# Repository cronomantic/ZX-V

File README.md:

**English** · [Español](README.es.md)

<h1 align="center">
  <picture>
    <source media="(prefers-color-scheme: dark)" srcset="docs/images/logo-dark.svg">
    
  </picture>
</h1>

A 32-bit hobby computer inspired by the ZX Spectrum. It is not a Spectrum
clone or a Spectrum emulator: it is a new machine that keeps the spirit of the
original — switch it on and you are in BASIC, ready to type a program.

- **The Spectrum's 15 colours, without colour clash:** every pixel has its own
  colour.
- **A BASIC compatible with Sinclair BASIC** (as far as is reasonable), with a
  full-screen editor and many extensions: structured loops, procedures,
  sprites, tile maps, scrolling, music and files.
- **Sound** from two AY-3-8912 chips and the beeper.
- **An SD card** instead of the tape: it also loads the Spectrum's `.TAP` and
  `.TZX` files. Examples and games come built in, on the `ROM:` drive.
- **Native programs in C** for its RISC-V CPU — the equivalent of Z80 machine
  code games — with an SDK, and BASIC compiled with
  [ZX Basic](docs/en/zxbasic.md).
- **An emulator** for Windows, Linux and the web browser.
- **Real hardware** built with two Raspberry Pi Pico 2 boards: one is the CPU,
  the other the "ULA" (video and sound).

> **Status:** the emulator and the ROM with BASIC work, and so does the first
> printed circuit board, with the two Picos together: the picture, the sound,
> the USB ports, the microSD card, the clock with its coin cell and loading
> from the PC through J5.

## Try it

**In your browser:** [zx-v.org/emulator](https://zx-v.org/emulator/),
nothing to install. The project's website, with its games to play right
there, is [zx-v.org](https://zx-v.org/).

**On your computer:** download the latest version from
[**Releases**](https://github.com/cronomantic/ZX-V/releases):

| Package | What it is |
|---|---|
| `zxv-windows-x64.zip` | The emulator for Windows, with the ROM and the examples |
| `zxv-linux-x86_64.tar.gz` and the `.AppImage` | The emulator for Linux |
| `zxv-web.zip` | The web version: unzip it and open `index.html` (no server needed) |
| `zxv-uf2.zip` | The firmware for the two Picos of the real machine |

Open it and you are in BASIC. Type this, pressing Enter after each line:

```
10 FOR i=1 TO 8: CIRCLE INK i;128,88,i*10: NEXT i
RUN
```

Then try `CAT "ROM:"` to see the built-in examples and games... or start with
the [getting started guide](docs/en/getting-started.md).

## Documentation

| | |
|---|---|
| [Getting started](docs/en/getting-started.md) | From zero to your first program |
| [Learn BASIC](docs/en/basic/README.md) | A course from scratch, step by step |
| [BASIC reference](docs/en/basic/reference.md) · [The editor](docs/en/basic/editor.md) | Every statement and function |
| [Native programs (SDK)](docs/en/sdk/README.md) | Programming the machine in C |
| [Graphics](docs/en/sdk/graphics.md#the-graphics-editor-for-the-pc-zxv-gfx) · [Music](docs/en/sdk/README.md#the-tracker-for-the-pc-zxv-tracker) | The editors for the PC: `zxv-gfx` and `zxv-tracker` |
| [Compiling BASIC](docs/en/zxbasic.md) | ZX Basic, with a target for ZX-V |
| [The emulator](docs/en/emulator.md) | The desktop and web versions, options |
| [The machine](docs/en/machine.md) | Screen, colours, sound, memory and files |
| [Build the hardware](docs/en/hardware/README.md) | The board, assembly and firmware |

All of it is also in Spanish: [docs/es](docs/es/README.md). And on the
web, with an index to move around: [zx-v.org/docs](https://zx-v.org/docs/en/).

## How it is made

```
┌────────── Pico 2 "CPU" ──────────┐   8-bit link + clock   ┌────────── Pico 2 "ULA" ──────────┐
│ the ROM: BASIC and the system    │───────────────────────►│ video: HDMI / DVI                │
│ your programs                    │   sound line           │ sound: two AY chips + beeper     │
│ USB keyboard, mouse and gamepads │───────────────────────►│        over HDMI and line out    │
│ SD card, clock                   │◄───────────────────────│                                  │
└──────────────────────────────────┘   frame sync, return   └──────────────────────────────────┘
```

For software there is a single machine; that it is made of two chips is a
detail of the hardware, and the emulator implements the same machine in one
program.

## What is here

| | |
|---|---|
| [`sdk/`](sdk) | The SDK for native programs in C, with its examples and eight complete games in C. MIT licence ([`sdk/LICENSE`](sdk/LICENSE)): your programs can have any licence |
| [`examples/`](examples) | Games in BASIC (`basic/`) and two in compiled BASIC with ZX Basic (`zxbasic/stardust` and `zxbasic/petitsoccer`). MIT licence ([`examples/LICENSE`](examples/LICENSE)) |
| [`docs/`](docs) | The documentation, in English and Spanish. CC BY 4.0 licence ([`docs/LICENSE`](docs/LICENSE)), the same as `dev/`; its code examples are public domain |
| [`pcb/`](pcb) | The printed circuit board, revision 1: the KiCad project, the files to order it from JLCPCB and the scripts that made it. Open hardware, CERN-OHL-W v2 licence ([`pcb/LICENSE`](pcb/LICENSE), with the exceptions in [`pcb/NOTICE`](pcb/NOTICE)); the scripts, MIT |
| [`dev/`](dev) | The technical specification of the machine ([`spec.md`](dev/spec.md)) and of its BASIC ([`basic.md`](dev/basic.md)), in Spanish: memory map, registers, the ROM API, file formats |
| [Releases](https://github.com/cronomantic/ZX-V/releases) | The emulator, the ROM and the firmware, as binaries. Free, and you can pass them on unchanged and free of charge: the terms are in [`TERMS.txt`](TERMS.txt) |

The source code of the emulator, the ROM and the firmware is not public. The
packages say in their `THIRD_PARTY_NOTICES.txt` what they contain that belongs
to others, with the texts of those licences.

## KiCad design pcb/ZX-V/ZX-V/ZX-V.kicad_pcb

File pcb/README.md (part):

# La placa de ZX-V

> **Using ZX-V?** See the board guide: [English](../docs/en/hardware/board.md) · [Español](../docs/es/hardware/board.md). This page is developer documentation, in Spanish.  
> **¿Usas ZX-V?** Mira la guía de la placa: [English](../docs/en/hardware/board.md) · [Español](../docs/es/hardware/board.md). Esta página es documentación de desarrollo.

**Estado: revisión 1 (v0.1), fabricada y probada:** con las dos Pico pasa `boardtest`, usa la tarjeta microSD y, con la pila, el reloj guarda la hora. Licencia CERN-OHL-W v2 (§8). El esquema (85 piezas en
tres hojas: alimentación, Pico CPU y Pico ULA) lo dibuja `tools/schematic.py`,
con ERC sin errores y cada pieza con su número LCSC. Las huellas que no traía
KiCad están en `zxv.pretty`, comprobadas con los planos. La placa la ponen al
día `tools/netlist_to_board.py` (del netlist), `tools/place.py` (contorno,
taladros, reglas y el sitio de cada pieza) y `tools/silkscreen.py` (los
rótulos propios y las referencias, cada una en un hueco libre). El rutado, en
dos pasos (§4.6): `tools/pairs.py` traza a mano los pares diferenciales (los
cuatro del HDMI y el del USB), y `tools/route.py` pasa el resto a Freerouting y
pone la masa: un plano en cada cara y vías de cosido. DRC: paridad con el
esquema, 0; nada sin conectar, sin errores de margen ni de serigrafía. Solo
queda el aviso de que las Pico no coinciden con su huella de la biblioteca: es
la marca *DNP* que les pone el esquema. Las dos Pico 2 y todo lo de la
protoboard en una placa. Los pines, los valores y por qué son los que son
están en dev/hardware-pico.md; aquí, lo propio de
la placa. El proyecto de KiCad (10) está en `ZX-V/ZX-V/`.

---

## 1. Objetivos

- **Que la pueda montar cualquiera**, de tres maneras (decisiones D57):
  1. **Pedirla montada a JLCPCB:** todo es SMD de una cara, así que vale su
     montaje *Economic*, el barato. Llega con todo soldado salvo las dos
     Pico, que se sueldan con sus tiras de pines (THT, lo más fácil de
     soldar; §6.2).
  2. **Con soldador:** todo lo SMD se puede soldar a mano.
  3. **Con placa caliente u horno:** con el stencil, que se pide con las
     placas.
- **De 100 × 100 mm o menos**, el tamaño más barato de JLCPCB, y **de dos
  capas**, con plano de masa.
- **Todo lo de la protoboard**, y nada que el firmware no use, salvo lo que
  cuesta un par de pads (§3).

---

## 2. Reglas del diseño

- **Todo lo SMD en la cara de arriba:** una placa caliente no suelda las dos
  caras, y JLCPCB monta una sola más barato.
- **Nada pequeño:** pasivos de 0805 con las huellas `_HandSolder` (los pads
  más largos); chips en SOIC, SOT-23 o SOD-123, sin QFN ni pads escondidos
  debajo. Sitio alrededor de cada pieza para la punta del soldador. La
  excepción, el cristal del reloj (3,2 × 1,5 mm, dos pads): es la pieza
  *Basic*, y se suelda bien con flux.
- **Cada pieza SMD con su número LCSC**, en el campo `LCSC` del símbolo. Las
  *Basic* de JLCPCB siempre que se pueda: las *Extended* cuestan más al
  montar.
- **Nada THT en el montaje:** JLCPCB cobra aparte cada soldadura THT, y con
  una sola el pedido ya no vale para el *Economic*. Solo son THT las tiras
  de las Pico (no los hay SMD de 1 × 20), las tiras opcionales y los mandos
  y LED del frontal (en ángulo recto, para que salgan por la caja), y los
  suelda quien la monta: van marcados *DNP*.
- **La serigrafía**, para montarla sin el esquema: referencias y valores, la
  polaridad de diodos, LED, condensadores y pila, los nombres de los
  conectores y los de los pines de las tiras.
- **En el repositorio**, con cada versión: el esquema en PDF, el BOM y el CPL
  de JLCPCB, los Gerber y la guía de montaje (la de la placa, en
  [inglés](../docs/en/hardware/board.md) y en [español](../docs/es/hardware/board.md)).

---

## 3. Decisiones de la placa (propuestas)

| Qué | Propuesta | Por qué |
|---|---|---|
| Las Pico | **Con tiras macho de 1 × 20**, soldadas a la Pico y a los taladros de la placa, o **por sus bordes almenados**: la huella común de KiCad (`RaspberryPi_Pico_Common_Unspecified`) tiene a la vez los taladros y los pads, y una zona libre para el enchufe del micro-USB. Va copiada en `zxv:RaspberryPi_Pico2_Common`, sin la zona prohibida de la antena de la Pico W, que la Pico 2 no tiene | Con las tiras, lo de siempre: separada de la placa, quedan a mano el micro-USB, el BOOTSEL y el conector de depuración (SWD) para el cable de programar. Almenada, la mitad de soldaduras y más baja |
| Módulos | **Ninguno:** la microSD, el reloj y el HDMI, en la placa | Más barato, más bajo y sin cables |
| Alimentación | **USB-C solo para la corriente**, de 5 V | Vale cualquier cargador de 2 A; no hay que comprar una fuente aparte |
| Capas | **Dos**, con plano de masa en las dos caras | El HDMI sale de GPIO con una resistencia en serie y pistas de 2 a 3 cm: los pares van acoplados, igualados y con el plano entero debajo (§4.6), pero sin impedancia controlada (con el plano a 1,5 mm no se llega a 100 Ω), que a 252 Mbit/s no decide. El USB es de 12 Mbit/s |
| Reinicio | **Un pulsador** a los RUN de las dos Pico | Sin desenchufar; Ctrl+Alt+Supr reinicia toda la Pico CPU, pero no la ULA |
| Encendido | **Un deslizante** (SW3) que manda un MOSFET P (Q1) entre el USB-C y los 5 V | El deslizante no aguanta 1 A; Q1 sí, y con arranque suave |
| Los mandos | **Delante**, lo que toca el usuario: USB-A, pulsadores, encendido y LED, **THT en ángulo recto** que asoman por el borde (el botón de los pulsadores, 4 mm; la palanca del deslizante, 3,4; la punta de los LED, 1). La microSD, en el lateral derecho | Para la caja: salen por agujeros del frontal, sin guías de luz ni capuchones. Los SMD de pulsación lateral y los LED de 0805 se quedaban dentro. Detrás, lo que se enchufa una vez |
| Sujeción | **Cuatro taladros M3** en las esquinas (redondeadas, de 3 mm) | Para los separadores de una caja o unos pies |
| La tarjeta | Su **contacto de detección**, a GP21 de la CPU (libre) | El firmware de la CPU monta y desmonta la tarjeta al ponerla y quitarla; sin el cable (la protoboard), va como antes |
| El I2C | **Una tira de 4 pines** (3V3, GND, SDA, SCL), sin montar | Para mirar el bus del reloj o para un módulo DS3231 (tiene preferencia, §4.2). Los programas no tienen acceso al I2C: otro módulo no lo usaría nadie |

---

## 4. Bloques

### 4.1 Alimentación

- **J1, USB-C** (solo VBUS, GND y CC): una resistencia de 5,1 kΩ de cada CC
  a masa, para que el cargador dé los 5 V. 10 µF a la entrada.
- **El encendido:** el deslizante SW3 (ON con la palanca a la derecha, vista
  desde delante: su pin 3, el de la derecha, va a masa) pone a masa, por R41 (10 kΩ), la puerta
  de Q1 (AO3401A, MOSFET P), que conduce de la entrada al raíl de 5 V. R40
  (100 kΩ) la apaga, y C16 (100 nF) con R41 da un arranque suave de ~1 ms. A
  la salida, 10 µF y 100 nF.
- **El raíl de 5 V** alimenta:
  - **Las dos Pico por VSYS** (pin 39), cada una por un **Schottky** (D1 y
    D2, SOD-123): así se puede enchufar el micro-USB de una Pico a la vez
    sin que sus 5 V vuelvan al raíl.
  - **El VBUS del USB-A**, por un **fusible rearmable de 500 mA** (F1), con
    dos de 22 µF y 100 nF.
  - **El pin 18 del HDMI** (la EDID del monitor), por otro Schottky (D3):
    que la tele no alimente la placa; y por un **fusible rearmable de
    200 mA** (F2, salta a 0,5 A como pide la norma): un cable o un
    adaptador en corto no se lleva los 5 V de la placa.
- **El micro-USB de una Pico, solo con la placa encendida.** Con ella
  apagada, una Pico sola alimentaría a la otra por los pines del enlace (y
  el RESET de las dos va unido).
- **Los 3,3 V** salen de la Pico CPU (3V3 OUT, pin 36) y alimentan la
  microSD, el reloj y las *pull-up* del I2C. **Los 3V3 de las dos Pico no se
  unen.**
- **El consumo**, calculado: las dos Pico, unos 100–150 mA; la tarjeta, hasta
  unos 100 mA (más en picos); los aparatos USB, hasta los 500 mA del
  fusible. Menos de 1 A en total.

### 4.2 Pico CPU (U1)

| Bloque | Piezas | Notas |
|---|---|---|
| microSD (SPI0, GP0–GP3) | Zócalo *push-push* Hirose DM3AT (J3), 10 kΩ de *pull-up* en CMD, DAT0–DAT3, 100 nF y 10 µF | El contacto de detección, a GP21 (§3) |
| USB host (GP14 D+, GP15 D−) | USB-A hembra SMD en ángulo recto (J4), 22 Ω en serie en cada línea y un TVS de protección sobre cada una, justo antes del conector (D5, D6; SOD-323) | El par, diferencial (§4.6). Las *pull-down* son las de la Pico. Primero era un SRV05-4, pero con sus patas una línea tenía que cruzar a la otra |
| Reloj (I2C0, GP16 SDA, GP17 SCL) | PCF8563 o BM8563 (U3, SOIC-8), cristal de 32,768 kHz de 12,5 pF, BAT54C, 100 nF, portapilas CR2032 (BT1), 4,7 kΩ de *pull-up* en SDA y SCL | dev/hardware-pico.md §7. Cristal de 3,2 × 1,5 mm (§2). CLKOUT e INT, sin conectar |
| LED de la tarjeta (GP22) | LED THT de 3 mm, verde, tumbado, y 330 Ω | |
| Carga remota (UART0: GP12 TX, GP13 RX) | Tira de 3 pines con GND (J5), sin montar | Programas desde el PC con `zxv-link` y un adaptador USB-serie de 3,3 V (D101) |
| Tira I2C | 4 pines (J6), sin montar | §3 |

### 4.3 Pico ULA (U2)

| Bloque | Piezas | Notas |
|---|---|---|
| HDMI (GP12–GP19, HSTX) | Conector HDMI tipo A, SMD (J7), una resistencia en serie por señal (8) | 240 Ω, como en dev/hardware-pico.md. Junto a la Pico, pares juntos y cortos. GND en 2, 5, 8, 11 y 17; 5 V en 18 (§4.1); HPD (19) a GP22 de la ULA (1 kΩ, R42, y 100 kΩ a masa, R43: GP22 admite 5 V); CEC (13) y DDC (15, 16), sin conectar |
| Audio PWM (GP2 izquierda, GP3 derecha) | Por canal: 1 kΩ, 10 nF, 10 kΩ, 1 nF, 10 µF en serie y 100 kΩ a masa; jack estéreo de 3,5 mm PJ-320D (J8, SMD de pads grandes) | dev/hardware-pico.md §6.2. Lejos del HDMI y de la fuente de la Pico, con su masa |
| Pulsador del modo (GP0) | Pulsador THT de 6 × 6 mm en ángulo recto (SW2) a masa | La *pull-up* es la interna |
| LED del enlace (GP1) | LED THT de 3 mm, rojo, tumbado, y 330 Ω | Unos 4 mA: lo que da el GPIO con su fuerza por defecto |

### 4.4 El enlace

- **Las señales:** D0–D7 (GP4–GP11) y CLK (GP26) de la CPU a la ULA, VBLANK
  (GP27) de la ULA a la CPU, la línea del sonido (GP20 de la CPU → GP21 de la
  ULA) y el canal de vuelta (GP20 de la ULA → GP18 de la CPU).
- **33 Ω en serie junto al que envía** (12): diez en la CPU (datos, CLK y la
  línea del sonido) y dos en la ULA (VBLANK y el canal de vuelta).
- **Pistas cortas sobre el plano de masa:** en la misma placa son unos
  centímetros, muy por debajo de los 20 cm de la protoboard.

### 4.5 Los bordes

Placa de 100 × 100 mm (el tamaño más barato de JLCPCB), con las esquinas
redondeadas (3 mm) y cuatro taladros M3 en ellas, a 4 mm de los bordes.

- **Delante, lo que toca el usuario:** el USB-A en el centro; a la izquierda,
  el encendido y el pulsador del modo (ULA); a la derecha, el reinicio y los
  LED de la tarjeta y del enlace. Todo THT en ángulo recto, asomando por el
  borde para salir por el frontal de la caja: el cuerpo de los pulsadores
  llega al borde y el botón sale 4 mm; el deslizante sale 0,8 mm y su
  palanca, 3,4; la punta de los LED, 1 mm. Cada lado tiene 20,8 mm, del
  taladro de la esquina a la zona del cable de la Pico, y va casi lleno.
- **Detrás, lo que se enchufa una vez:** el USB-C de la alimentación, el HDMI
  (detrás de la ULA, que saca el vídeo por los pines de ese extremo) y el jack.
- **En el lateral derecho:** la microSD (junto a sus pines de la CPU) y la
  pila.
- **Las dos Pico**, una al lado de la otra (la ULA a la izquierda), con el
  micro-USB hacia delante y su zona libre de 20 mm para el cable de
  programar; entre las dos zonas, el USB-A. El conector SWD, en el otro
  extremo. Entre las Pico, las resistencias del enlace.

### 4.6 El rutado

Desde la placa colocada (`netlist_to_board.py`, `place.py`, `silkscreen.py`),
cada paso en su proceso (el Python de KiCad falla a veces si carga dos placas
seguidas):

```
C:/KiCad/10.0/bin/python.exe pcb/tools/pairs.py pcb/ZX-V/ZX-V/ZX-V.kicad_pcb
C:/KiCad/10.0/bin/python.exe pcb/tools/route.py dsn pcb/ZX-V/ZX-V/ZX-V.kicad_pcb
C:/KiCad/10.0/bin/python.exe pcb/tools/route.py fr  pcb/ZX-V/ZX-V/ZX-V.kicad_pcb
C:/KiCad/10.0/bin/python.exe pcb/tools/route.py ses pcb/ZX-V/ZX-V/ZX-V.kicad_pcb
kicad-cli pcb drc --schematic-parity --refill-zones --save-board pcb/ZX-V/ZX-V/ZX-V.kicad_pcb
```

- **Los pares diferenciales, por coordenadas** (`pairs.py`), porque
  Freerouting no sabe de pares. Cada tramo (de dos pads a otros dos: de la
  Pico a las resistencias, y de ellas al conector) es una línea central con
  giros de 45°, y las dos líneas del par, paralelas a ella: separación
  constante también en las esquinas. HDMI, a 0,2 mm de ancho y 0,15 de
  separación: de los pines de la ULA, que se juntan por igual, a sus 240 Ω y
  al conector, en abanico, sin cruces; D1 y D0 pasan bajo la Pico. USB, a
  0,25 y 0,15: de GP14 y GP15 por dentro de la columna de pines de la CPU a
  sus 22 Ω (una sobre otra, en el camino) y al USB-A, con cada diodo de
  protección sobre su línea, sin rabos.
- **Largo igualado:** en cada giro la línea de dentro se queda más corta (un
  giro de 90° deja 0,58 mm en el HDMI); la más corta lleva una onda de
  esquinas a 45° que la iguala, en cada tramo por separado. Diferencia: 0,000
  mm en todos.
- **Las reglas, en KiCad:** las redes de los pares acaban en P y N
  (`ULA_D2P`/`ULA_D2N`, `HDMI_D2P`/`HDMI_D2N`, `USB_DP`/`USB_DN`,
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
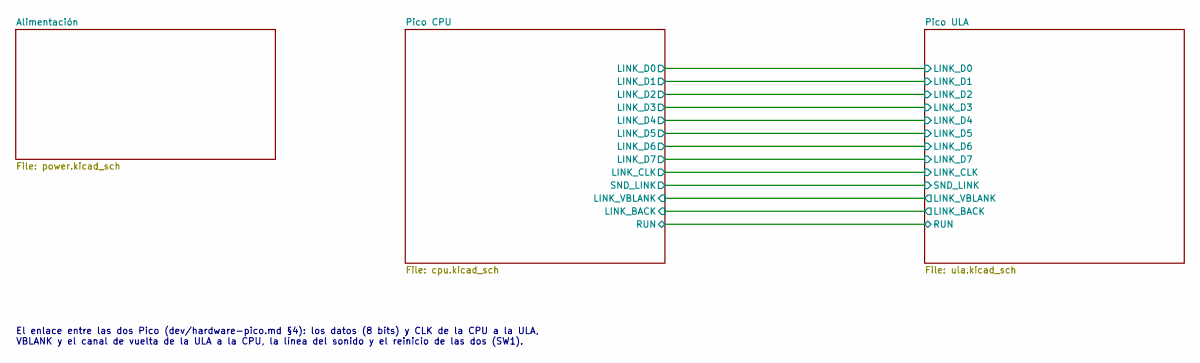
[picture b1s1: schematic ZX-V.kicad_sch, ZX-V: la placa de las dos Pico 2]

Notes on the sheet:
El enlace entre las dos Pico (dev/hardware-pico.md §4): los datos (8 bits) y CLK de la CPU a la ULA, VBLANK y el canal de vuelta de la ULA a la CPU, la línea del sonido y el reinicio de las dos (SW1).

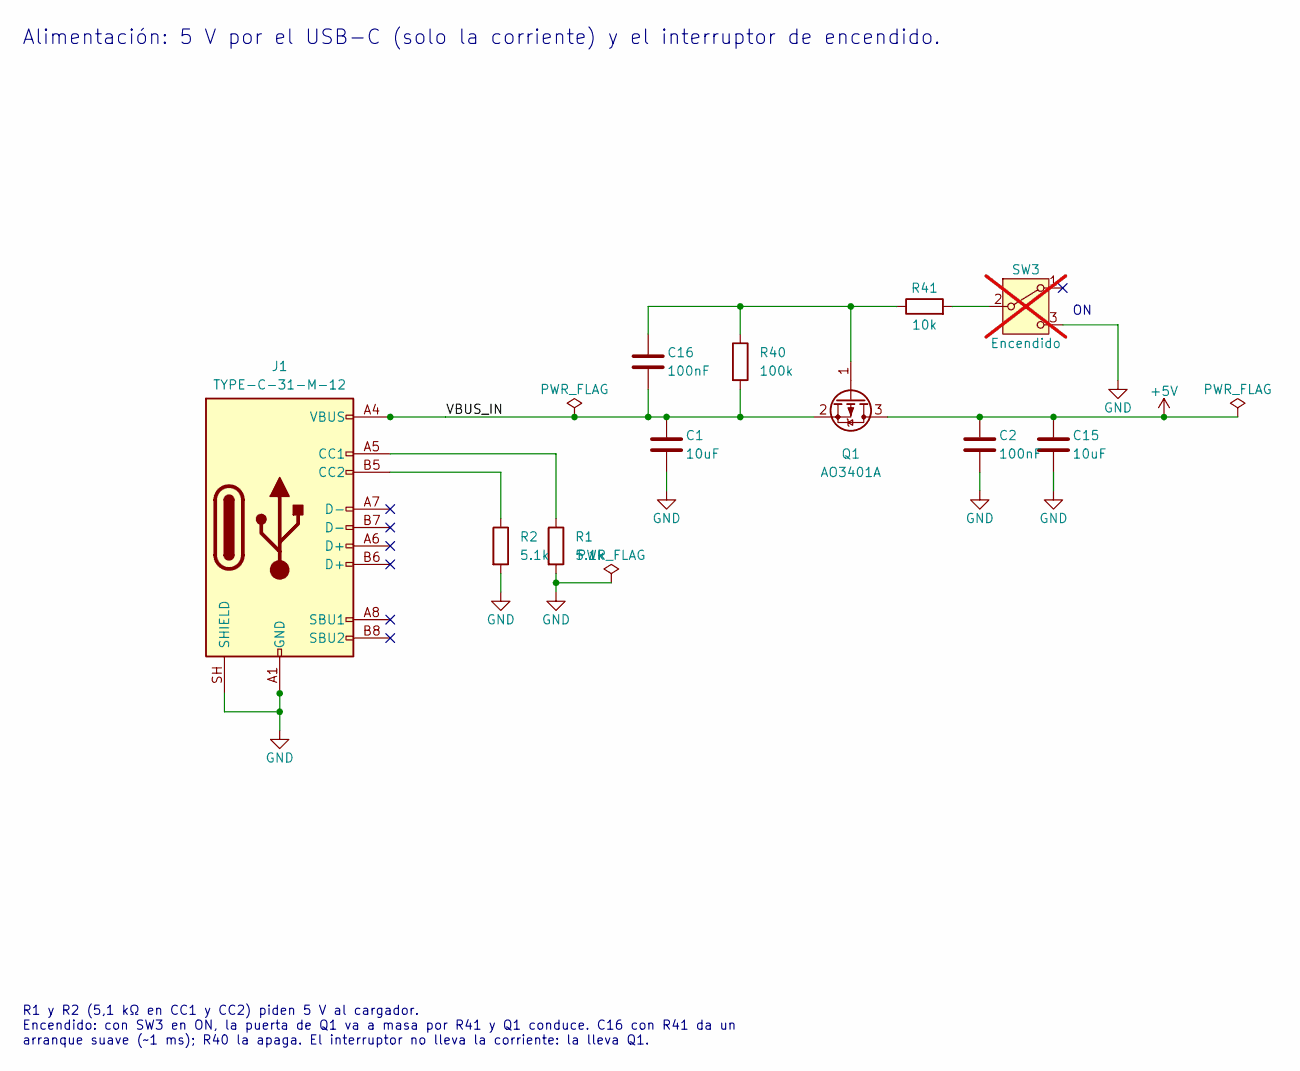
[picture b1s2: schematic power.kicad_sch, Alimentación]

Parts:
C1, C15: 10uF; C_0805_2012Metric_Pad1.18x1.45mm_HandSolder; LCSC C15850
C2, C16: 100nF; C_0805_2012Metric_Pad1.18x1.45mm_HandSolder; LCSC C49678
J1: TYPE-C-31-M-12; USB_C_Receptacle_HRO_TYPE-C-31-M-12; LCSC C165948
Q1: AO3401A; SOT-23; LCSC C15127
R1, R2: 5.1k; R_0805_2012Metric_Pad1.20x1.40mm_HandSolder; LCSC C27834
R40: 100k; R_0805_2012Metric_Pad1.20x1.40mm_HandSolder; LCSC C149504
R41: 10k; R_0805_2012Metric_Pad1.20x1.40mm_HandSolder; LCSC C17414
SW3: Encendido; SW_Slide_SK12D07VG4_Angled; LCSC C393937; not fitted

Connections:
+5V: C2.1, C15.1, Q1.3 (D); also elsewhere on the board
/Alimentación/VBUS_IN: C1.1, C16.2, J1.A4 (VBUS), J1.A9 (VBUS), J1.B4 (VBUS), J1.B9 (VBUS), Q1.2 (S), R40.2
GND: C1.2, C2.2, C15.2, J1.A1 (GND), J1.A12 (GND), J1.B1 (GND), J1.B12 (GND), J1.SH (SHIELD), R1.2, R2.2, SW3.3 (C); also elsewhere on the board
unnamed: J1.A5 (CC1), R1.1
unnamed: J1.B5 (CC2), R2.1
unnamed: C16.1, Q1.1 (G), R40.1, R41.1
unnamed: R41.2, SW3.2 (B)

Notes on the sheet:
Alimentación: 5 V por el USB-C (solo la corriente) y el interruptor de encendido.
R1 y R2 (5,1 kΩ en CC1 y CC2) piden 5 V al cargador. Encendido: con SW3 en ON, la puerta de Q1 va a masa por R41 y Q1 conduce. C16 con R41 da un arranque suave (~1 ms); R40 la apaga. El interruptor no lleva la corriente: la lleva Q1.

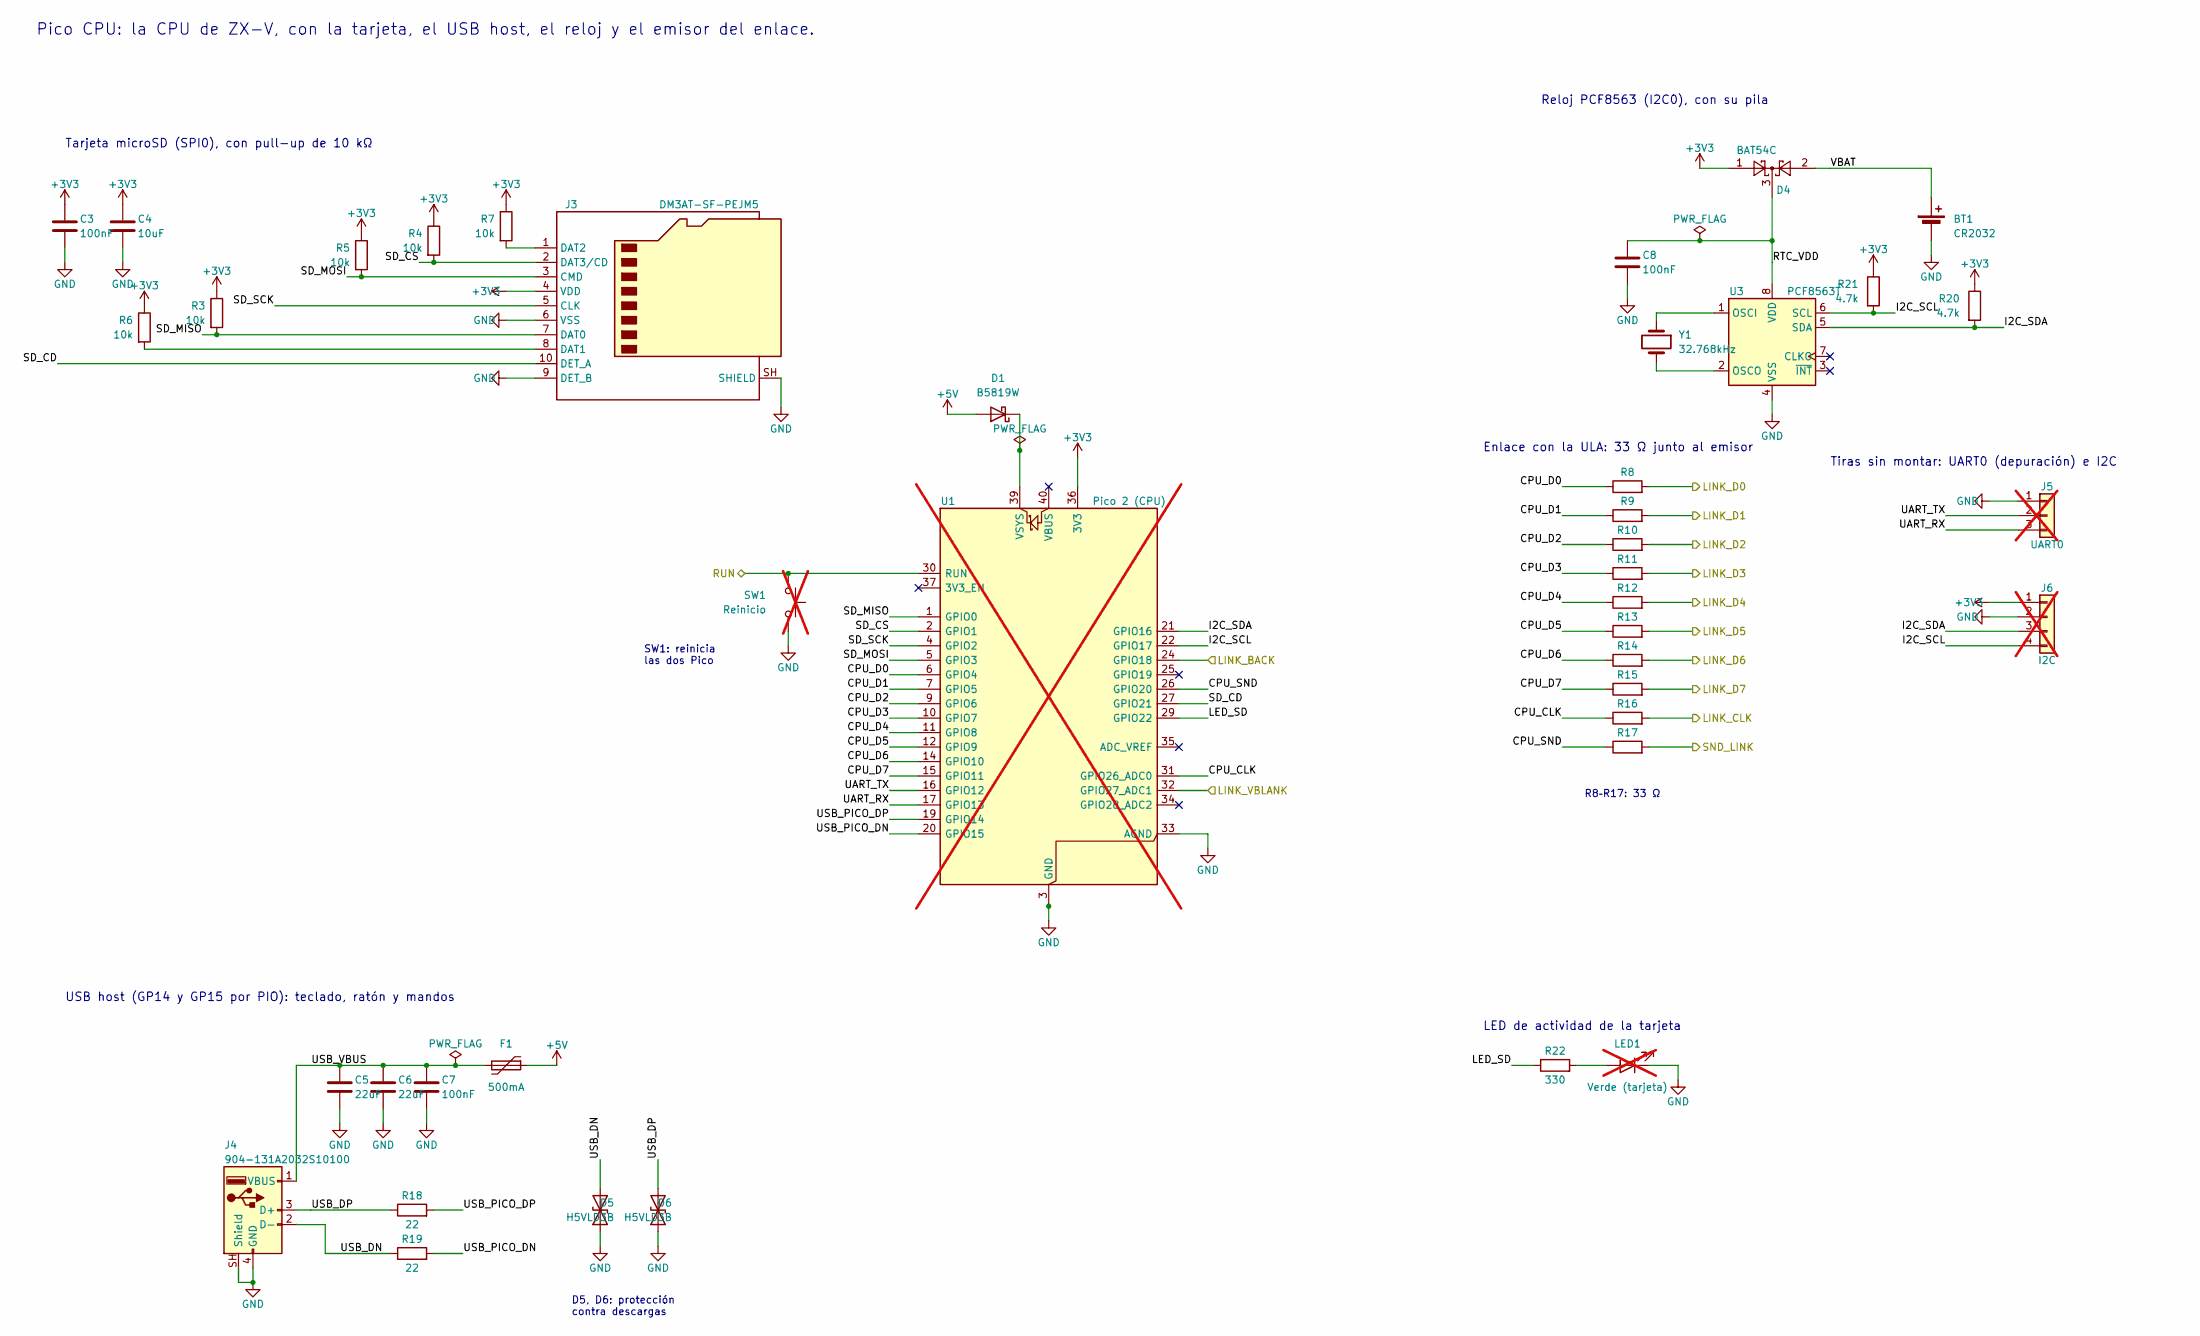
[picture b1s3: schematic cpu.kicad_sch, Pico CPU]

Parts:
BT1: CR2032; BatteryHolder_CR2032-BS-6-1; LCSC C22363833
C3, C7, C8: 100nF; C_0805_2012Metric_Pad1.18x1.45mm_HandSolder; LCSC C49678
C4: 10uF; C_0805_2012Metric_Pad1.18x1.45mm_HandSolder; LCSC C15850
C5, C6: 22uF; C_1206_3216Metric_Pad1.33x1.80mm_HandSolder; LCSC C12891
D1: B5819W; D_SOD-123; LCSC C8598
D4: BAT54C; SOT-23; LCSC C37704
D5, D6: H5VLD3B; D_SOD-323; LCSC C20615805
F1: 500mA; Fuse_1206_3216Metric_Pad1.42x1.75mm_HandSolder; LCSC C720075
J3: DM3AT-SF-PEJM5; microSD_HC_Hirose_DM3AT-SF-PEJM5; LCSC C114218
J4: 904-131A2032S10100; USB_A_904-131A2032S10100; LCSC C8328
J5: UART0; PinHeader_1x03_P2.54mm_Vertical; not fitted
J6: I2C; PinHeader_1x04_P2.54mm_Vertical; not fitted
LED1: Verde (tarjeta); LED_D3.0mm_Horizontal_O1.27mm_Z2.0mm; LCSC C125082; not fitted
R3, R4, R5, R6, R7: 10k; R_0805_2012Metric_Pad1.20x1.40mm_HandSolder; LCSC C17414
R8, R9, R10, R11, R12, R13, R14, R15, R16, R17: 33; R_0805_2012Metric_Pad1.20x1.40mm_HandSolder; LCSC C17634
R18, R19: 22; R_0805_2012Metric_Pad1.20x1.40mm_HandSolder; LCSC C17561
R20, R21: 4.7k; R_0805_2012Metric_Pad1.20x1.40mm_HandSolder; LCSC C17673
R22: 330; R_0805_2012Metric_Pad1.20x1.40mm_HandSolder; LCSC C17630
SW1: Reinicio; SW_SPST_Omron_B3F-315x_Angled; LCSC C231320; not fitted
U1: Pico 2 (CPU); RaspberryPi_Pico2_Common; not fitted
U3: PCF8563T; SOIC-8_3.9x4.9mm_P1.27mm; LCSC C7440
Y1: 32.768kHz; Crystal_SMD_3215-2Pin_3.2x1.5mm; LCSC C271654

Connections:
+3V3: C3.1, C4.1, D4.1, J3.4 (VDD), J6.1, R3.1, R4.1, R5.1, R6.1, R7.1, R20.1, R21.1, U1.36 (3V3)
+5V: D1.2 (A), F1.1; also elsewhere on the board
/Pico CPU/CPU_CLK: R16.1, U1.31 (GPIO26_ADC0)
/Pico CPU/CPU_D0: R8.1, U1.6 (GPIO4)
/Pico CPU/CPU_D1: R9.1, U1.7 (GPIO5)
/Pico CPU/CPU_D2: R10.1, U1.9 (GPIO6)
/Pico CPU/CPU_D3: R11.1, U1.10 (GPIO7)
/Pico CPU/CPU_D4: R12.1, U1.11 (GPIO8)
/Pico CPU/CPU_D5: R13.1, U1.12 (GPIO9)
/Pico CPU/CPU_D6: R14.1, U1.14 (GPIO10)
/Pico CPU/CPU_D7: R15.1, U1.15 (GPIO11)
/Pico CPU/CPU_SND: R17.1, U1.26 (GPIO20)
/Pico CPU/I2C_SCL: J6.4, R21.2, U1.22 (GPIO17), U3.6 (SCL)
/Pico CPU/I2C_SDA: J6.3, R20.2, U1.21 (GPIO16), U3.5 (SDA)
/Pico CPU/LED_SD: R22.1, U1.29 (GPIO22)
/Pico CPU/LINK_BACK: U1.24 (GPIO18); also elsewhere on the board
/Pico CPU/LINK_CLK: R16.2; also elsewhere on the board
/Pico CPU/LINK_D0: R8.2; also elsewhere on the board
/Pico CPU/LINK_D1: R9.2; also elsewhere on the board
/Pico CPU/LINK_D2: R10.2; also elsewhere on the board
/Pico CPU/LINK_D3: R11.2; also elsewhere on the board
/Pico CPU/LINK_D4: R12.2; also elsewhere on the board
/Pico CPU/LINK_D5: R13.2; also elsewhere on the board
/Pico CPU/LINK_D6: R14.2; also elsewhere on the board
/Pico CPU/LINK_D7: R15.2; also elsewhere on the board
/Pico CPU/LINK_VBLANK: U1.32 (GPIO27_ADC1); also elsewhere on the board
/Pico CPU/RTC_VDD: C8.1, D4.3, U3.8 (VDD)
/Pico CPU/RUN: SW1.1, U1.30 (RUN); also elsewhere on the board
/Pico CPU/SD_CD: J3.10 (DET_A), U1.27 (GPIO21)
/Pico CPU/SD_CS: J3.2 (DAT3/CD), R4.2, U1.2 (GPIO1)
/Pico CPU/SD_MISO: J3.7 (DAT0), R3.2, U1.1 (GPIO0)
/Pico CPU/SD_MOSI: J3.3 (CMD), R5.2, U1.5 (GPIO3)
/Pico CPU/SD_SCK: J3.5 (CLK), U1.4 (GPIO2)
/Pico CPU/SND_LINK: R17.2; also elsewhere on the board
/Pico CPU/UART_RX: J5.3, U1.17 (GPIO13)
/Pico CPU/UART_TX: J5.2, U1.16 (GPIO12)
/Pico CPU/USB_DN: D5.2 (A2), J4.2 (D-), R19.1
/Pico CPU/USB_DP: D6.2 (A2), J4.3 (D+), R18.1
/Pico CPU/USB_PICO_DN: R19.2, U1.20 (GPIO15)
/Pico CPU/USB_PICO_DP: R18.2, U1.19 (GPIO14)
/Pico CPU/USB_VBUS: C5.1, C6.1, C7.1, F1.2, J4.1 (VBUS)
/Pico CPU/VBAT: BT1.1 (+), D4.2
GND: BT1.2 (-), C3.2, C4.2, C5.2, C6.2, C7.2, C8.2, D5.1 (A1), D6.1 (A1), J3.6 (VSS), J3.9 (DET_B), J3.SH (SHIELD), J4.4 (GND), J4.SH (Shield), J5.1, J6.2, LED1.1 (K), SW1.2, U1.3 (GND), U1.8 (GND), U1.13 (GND), U1.18 (GND), U1.23 (GND), U1.28 (GND), U1.33 (AGND), U1.38 (GND), U3.4 (VSS); also elsewhere on the board
unnamed: D1.1 (K), U1.39 (VSYS)
unnamed: J3.8 (DAT1), R6.2
unnamed: J3.1 (DAT2), R7.2
unnamed: LED1.2 (A), R22.2
unnamed: U3.1 (OSCI), Y1.1
unnamed: U3.2 (OSCO), Y1.2

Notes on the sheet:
Pico CPU: la CPU de ZX-V, con la tarjeta, el USB host, el reloj y el emisor del enlace.
SW1: reinicia las dos Pico
Tarjeta microSD (SPI0), con pull-up de 10 kΩ
USB host (GP14 y GP15 por PIO): teclado, ratón y mandos
D5, D6: protección contra descargas
Enlace con la ULA: 33 Ω junto al emisor
R8–R17: 33 Ω
Reloj PCF8563 (I2C0), con su pila
Tiras sin montar: UART0 (depuración) e I2C
LED de actividad de la tarjeta

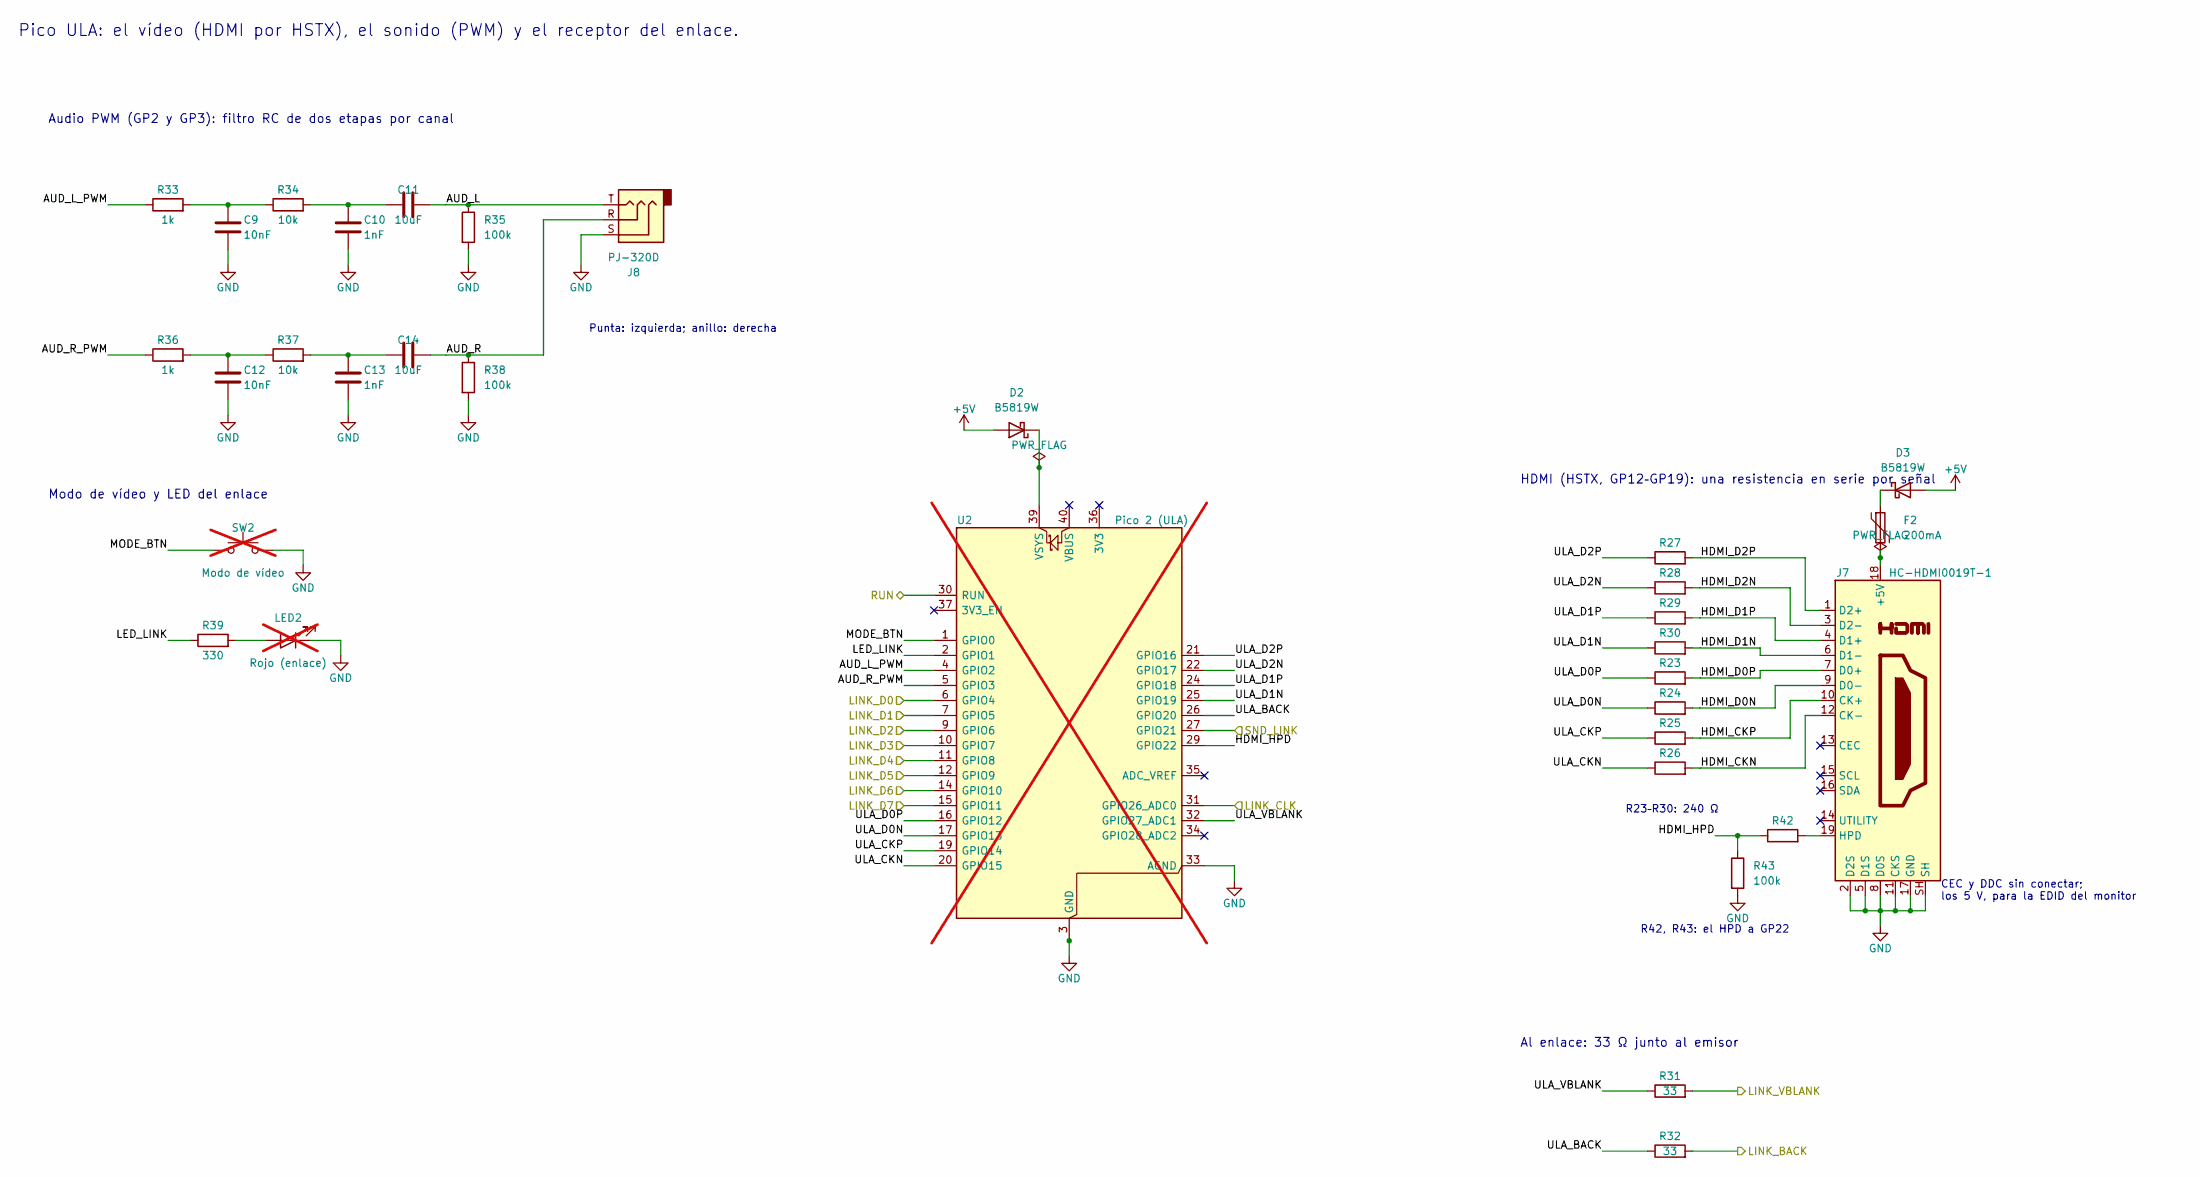
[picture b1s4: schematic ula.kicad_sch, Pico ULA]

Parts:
C9, C12: 10nF; C_0805_2012Metric_Pad1.18x1.45mm_HandSolder; LCSC C1710
C10, C13: 1nF; C_0805_2012Metric_Pad1.18x1.45mm_HandSolder; LCSC C46653
C11, C14: 10uF; C_0805_2012Metric_Pad1.18x1.45mm_HandSolder; LCSC C15850
D2, D3: B5819W; D_SOD-123; LCSC C8598
F2: 200mA; Fuse_0805_2012Metric_Pad1.15x1.40mm_HandSolder; LCSC C126816
J7: HC-HDMI0019T-1; HDMI_A_HC-HDMI0019T-1; LCSC C7501809
J8: PJ-320D; Jack_3.5mm_PJ-320D_TRS; LCSC C431535
LED2: Rojo (enlace); LED_D3.0mm_Horizontal_O1.27mm_Z2.0mm; LCSC C125081; not fitted
R23, R24, R25, R26, R27, R28, R29, R30: 240; R_0805_2012Metric_Pad1.20x1.40mm_HandSolder; LCSC C17572
R31, R32: 33; R_0805_2012Metric_Pad1.20x1.40mm_HandSolder; LCSC C17634
R33, R36, R42: 1k; R_0805_2012Metric_Pad1.20x1.40mm_HandSolder; LCSC C17513
R34, R37: 10k; R_0805_2012Metric_Pad1.20x1.40mm_HandSolder; LCSC C17414
R35, R38, R43: 100k; R_0805_2012Metric_Pad1.20x1.40mm_HandSolder; LCSC C149504
R39: 330; R_0805_2012Metric_Pad1.20x1.40mm_HandSolder; LCSC C17630
SW2: Modo de vídeo; SW_SPST_Omron_B3F-315x_Angled; LCSC C231320; not fitted
U2: Pico 2 (ULA); RaspberryPi_Pico2_Common; not fitted

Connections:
+5V: D2.2 (A), D3.2 (A); also elsewhere on the board
/Pico CPU/LINK_BACK: R32.2; also elsewhere on the board
/Pico CPU/LINK_CLK: U2.31 (GPIO26_ADC0); also elsewhere on the board
/Pico CPU/LINK_D0: U2.6 (GPIO4); also elsewhere on the board
/Pico CPU/LINK_D1: U2.7 (GPIO5); also elsewhere on the board
/Pico CPU/LINK_D2: U2.9 (GPIO6); also elsewhere on the board
/Pico CPU/LINK_D3: U2.10 (GPIO7); also elsewhere on the board
/Pico CPU/LINK_D4: U2.11 (GPIO8); also elsewhere on the board
/Pico CPU/LINK_D5: U2.12 (GPIO9); also elsewhere on the board
/Pico CPU/LINK_D6: U2.14 (GPIO10); also elsewhere on the board
/Pico CPU/LINK_D7: U2.15 (GPIO11); also elsewhere on the board
/Pico CPU/LINK_VBLANK: R31.2; also elsewhere on the board
/Pico CPU/RUN: U2.30 (RUN); also elsewhere on the board
/Pico CPU/SND_LINK: U2.27 (GPIO21); also elsewhere on the board
/Pico ULA/AUD_L: C11.2, J8.T, R35.1
/Pico ULA/AUD_L_PWM: R33.1, U2.4 (GPIO2)
/Pico ULA/AUD_R: C14.2, J8.R, R38.1
/Pico ULA/AUD_R_PWM: R36.1, U2.5 (GPIO3)
/Pico ULA/HDMI_CKN: J7.12 (CK-), R26.2
/Pico ULA/HDMI_CKP: J7.10 (CK+), R25.2
/Pico ULA/HDMI_D0N: J7.9 (D0-), R24.2
/Pico ULA/HDMI_D0P: J7.7 (D0+), R23.2
/Pico ULA/HDMI_D1N: J7.6 (D1-), R30.2
/Pico ULA/HDMI_D1P: J7.4 (D1+), R29.2
/Pico ULA/HDMI_D2N: J7.3 (D2-), R28.2
/Pico ULA/HDMI_D2P: J7.1 (D2+), R27.2
/Pico ULA/HDMI_HPD: R42.1, R43.1, U2.29 (GPIO22)
/Pico ULA/LED_LINK: R39.1, U2.2 (GPIO1)
/Pico ULA/MODE_BTN: SW2.1, U2.1 (GPIO0)
/Pico ULA/ULA_BACK: R32.1, U2.26 (GPIO20)
/Pico ULA/ULA_CKN: R26.1, U2.20 (GPIO15)
/Pico ULA/ULA_CKP: R25.1, U2.19 (GPIO14)
/Pico ULA/ULA_D0N: R24.1, U2.17 (GPIO13)
/Pico ULA/ULA_D0P: R23.1, U2.16 (GPIO12)
/Pico ULA/ULA_D1N: R30.1, U2.25 (GPIO19)
/Pico ULA/ULA_D1P: R29.1, U2.24 (GPIO18)
/Pico ULA/ULA_D2N: R28.1, U2.22 (GPIO17)
/Pico ULA/ULA_D2P: R27.1, U2.21 (GPIO16)
/Pico ULA/ULA_VBLANK: R31.1, U2.32 (GPIO27_ADC1)
GND: C9.2, C10.2, C12.2, C13.2, J7.2 (D2S), J7.5 (D1S), J7.8 (D0S), J7.11 (CKS), J7.17 (GND), J7.SH, J8.S, LED2.1 (K), R35.2, R38.2, R43.2, SW2.2, U2.3 (GND), U2.8 (GND), U2.13 (GND), U2.18 (GND), U2.23 (GND), U2.28 (GND), U2.33 (AGND), U2.38 (GND); also elsewhere on the board
unnamed: C9.1, R33.2, R34.1
unnamed: C10.1, C11.1, R34.2
unnamed: C12.1, R36.2, R37.1
unnamed: C13.1, C14.1, R37.2
unnamed: D2.1 (K), U2.39 (VSYS)
unnamed: D3.1 (K), F2.1
unnamed: F2.2, J7.18 (+5V)
unnamed: J7.19 (HPD), R42.2
unnamed: LED2.2 (A), R39.2

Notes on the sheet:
Pico ULA: el vídeo (HDMI por HSTX), el sonido (PWM) y el receptor del enlace.
HDMI (HSTX, GP12–GP19): una resistencia en serie por señal
R23–R30: 240 Ω
CEC y DDC sin conectar; los 5 V, para la EDID del monitor
R42, R43: el HPD a GP22
Al enlace: 33 Ω junto al emisor
Audio PWM (GP2 y GP3): filtro RC de dos etapas por canal
Punta: izquierda; anillo: derecha
Modo de vídeo y LED del enlace

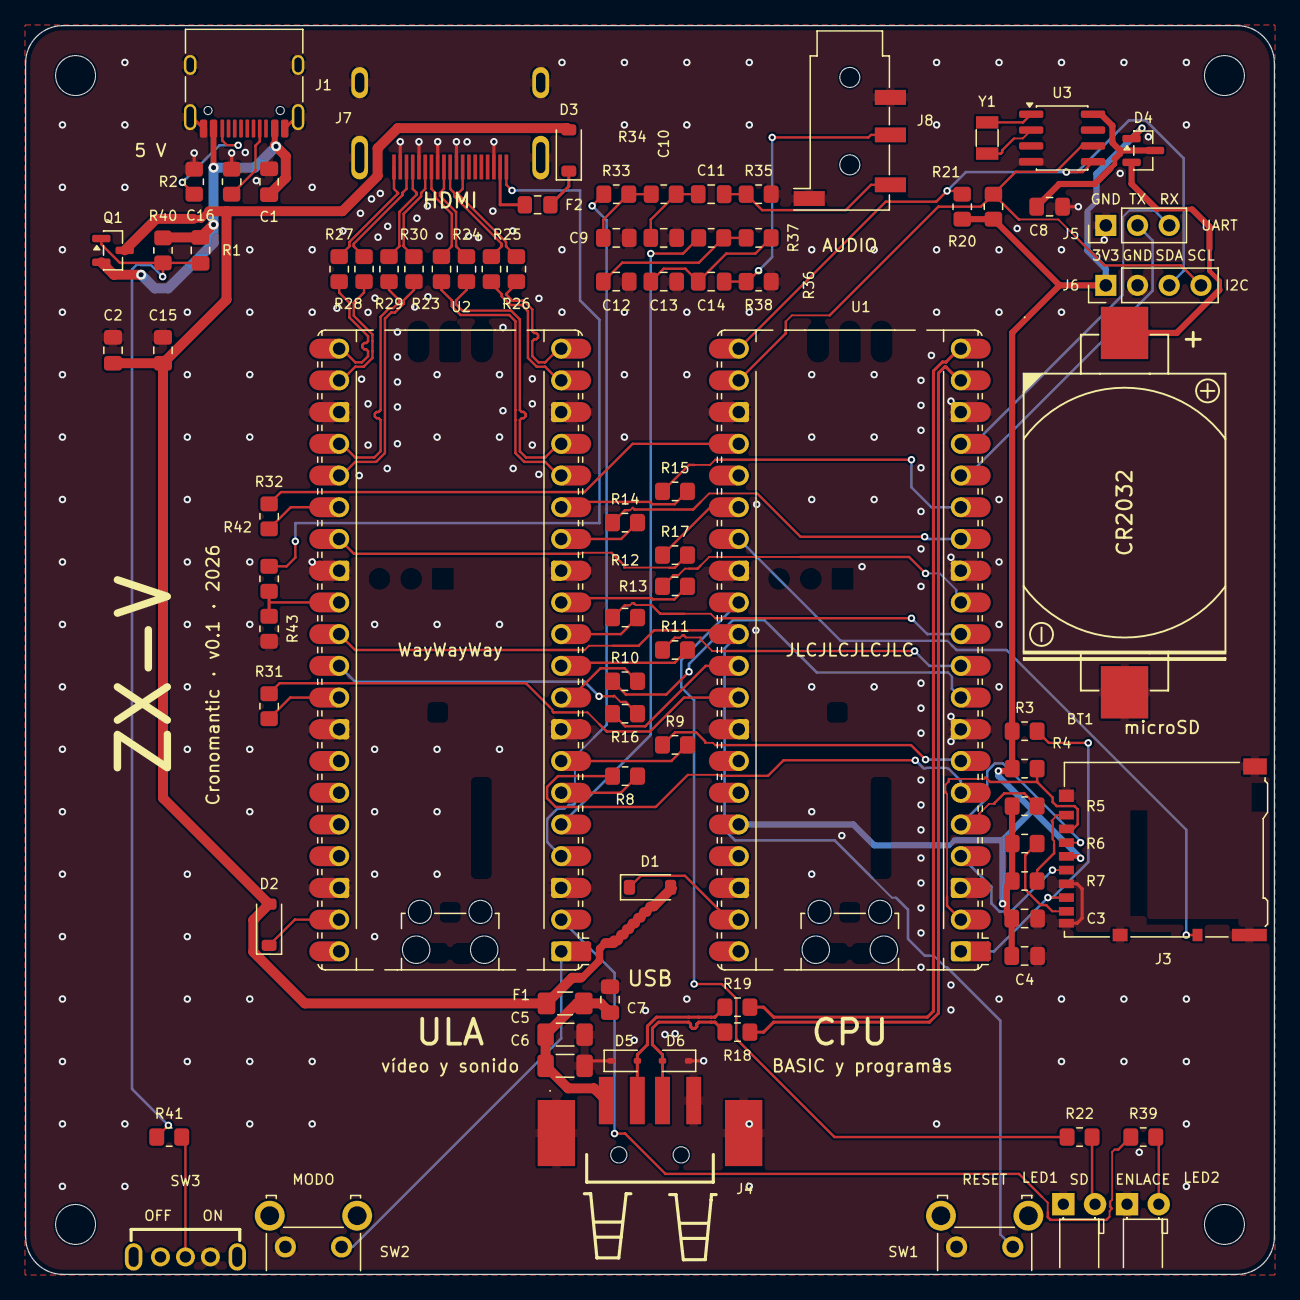
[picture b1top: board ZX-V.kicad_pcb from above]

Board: 2 copper layers, 100.0 x 100.0 mm, 89 parts (0 on the bottom side), 88 nets.

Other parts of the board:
H1, H2, H3, H4: MountingHole_3.2mm_M3

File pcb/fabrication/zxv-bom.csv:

Comment,Designator,Footprint,JLCPCB Part #（optional）
CR2032,BT1,BatteryHolder_CR2032-BS-6-1,C22363833
10uF,"C1,C4,C11,C14,C15",C_0805_2012Metric_Pad1.18x1.45mm_HandSolder,C15850
100nF,"C2,C3,C7,C8,C16",C_0805_2012Metric_Pad1.18x1.45mm_HandSolder,C49678
22uF,"C5,C6",C_1206_3216Metric_Pad1.33x1.80mm_HandSolder,C12891
10nF,"C9,C12",C_0805_2012Metric_Pad1.18x1.45mm_HandSolder,C1710
1nF,"C10,C13",C_0805_2012Metric_Pad1.18x1.45mm_HandSolder,C46653
B5819W,"D1,D2,D3",D_SOD-123,C8598
BAT54C,D4,SOT-23,C37704
H5VLD3B,"D5,D6",D_SOD-323,C20615805
500mA,F1,Fuse_1206_3216Metric_Pad1.42x1.75mm_HandSolder,C720075
200mA,F2,Fuse_0805_2012Metric_Pad1.15x1.40mm_HandSolder,C126816
TYPE-C-31-M-12,J1,USB_C_Receptacle_HRO_TYPE-C-31-M-12,C165948
DM3AT-SF-PEJM5,J3,microSD_HC_Hirose_DM3AT-SF-PEJM5,C114218
904-131A2032S10100,J4,USB_A_904-131A2032S10100,C8328
HC-HDMI0019T-1,J7,HDMI_A_HC-HDMI0019T-1,C7501809
PJ-320D,J8,Jack_3.5mm_PJ-320D_TRS,C431535
AO3401A,Q1,SOT-23,C15127
5.1k,"R1,R2",R_0805_2012Metric_Pad1.20x1.40mm_HandSolder,C27834
10k,"R3,R4,R5,R6,R7,R34,R37,R41",R_0805_2012Metric_Pad1.20x1.40mm_HandSolder,C17414
33,"R8,R9,R10,R11,R12,R13,R14,R15,R16,R17,R31,R32",R_0805_2012Metric_Pad1.20x1.40mm_HandSolder,C17634
22,"R18,R19",R_0805_2012Metric_Pad1.20x1.40mm_HandSolder,C17561
4.7k,"R20,R21",R_0805_2012Metric_Pad1.20x1.40mm_HandSolder,C17673
330,"R22,R39",R_0805_2012Metric_Pad1.20x1.40mm_HandSolder,C17630
240,"R23,R24,R25,R26,R27,R28,R29,R30",R_0805_2012Metric_Pad1.20x1.40mm_HandSolder,C17572
1k,"R33,R36,R42",R_0805_2012Metric_Pad1.20x1.40mm_HandSolder,C17513
100k,"R35,R38,R40,R43",R_0805_2012Metric_Pad1.20x1.40mm_HandSolder,C149504
PCF8563T,U3,SOIC-8_3.9x4.9mm_P1.27mm,C7440
32.768kHz,Y1,Crystal_SMD_3215-2Pin_3.2x1.5mm,C271654

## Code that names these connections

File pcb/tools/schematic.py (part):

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               fields={'Reference': (139.7, 83.82, None), 'Value': (139.7, 86.36, None)})
    vb, src, drn = J1.p('A4'), Q1.p('2'), Q1.p('3')
    s.wire(vb, src)
    s.label('VBUS_IN', (vb[0] + 7.62, vb[1]), 'R')
    s.pwr('PWR_FLAG', (101.6, vb[1]))
    s.sym('C1', 'Device:C', 114.3, vb[1] + 3.81, 0, value='10uF', footprint=C0805)
    s.wire((114.3, vb[1] + 7.62), (114.3, vb[1] + 10.16))
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    # Reinicio de las dos Pico
    run = U.p('30')
    s.wire(run, (149.86, run[1]))
    s.label('RUN', (149.86, run[1]), 'L', kind='hierarchical_label', shape='bidirectional')
    sy = run[1] + 5.08
    SW1 = s.sym('SW1', 'Switch:SW_Push', 157.48, sy, 270, value='Reinicio', footprint=PULSADOR, lcsc='C231320', dnp=True,
                fields={'Reference': (153.67, sy - 1.27, 'right'), 'Value': (153.67, sy + 1.27, 'right')})
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    R19 = s.sym('R19', 'Device:R', 91.44, dm[1] + 5.08, 90, value='22', footprint=R0805)
    s.wire(dp, R18.p('1'))
    s.wire(dm, (dm[0] + 5.08, dm[1]), (dm[0] + 5.08, dm[1] + 5.08), R19.p('1'))
    s.label('USB_DP', (dp[0] + 2.54, dp[1]), 'R')
    s.label('USB_DN', (dm[0] + 7.62, dm[1] + 5.08), 'R')
    for R, name in ((R18, 'USB_PICO_DP'), (R19, 'USB_PICO_DN')):
        p = R.p('2')
        s.wire(p, (p[0] + 5.08, p[1]))
        s.label(name, (p[0] + 5.08, p[1]), 'R')
    vy = 203.2
    s.wire(vb, (vb[0], vy), (104.14, vy))
    s.label('USB_VBUS', (vb[0] + 2.54, vy), 'R')
    s.pwr('PWR_FLAG', (99.06, vy))
    F1 = s.sym('F1', 'Device:Polyfuse', 107.95, vy, 270, value='500mA')
    s.wire(F1.p('1'), (116.84, vy))
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    p = C8.p('2')
    s.wire(p, (p[0], p[1] + 2.54))
    s.pwr('GND', (p[0], p[1] + 2.54))
    s.label('RTC_VDD', (vdd[0], 62.23), 'R')
    sda, scl = U3.p('5'), U3.p('6')
    s.wire(scl, (351.79, scl[1]))
    s.label('I2C_SCL', (351.79, scl[1]), 'R')
    s.wire(sda, (370.84, sda[1]))
    s.label('I2C_SDA', (370.84, sda[1]), 'R')
    for ref, x, line in (('R21', 347.98, scl), ('R20', 365.76, sda)):
        y = line[1] - 3.81
        R = s.sym(ref, 'Device:R', x, y, 0, value='4.7k', footprint=R0805,
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             '32': ('ULA_VBLANK', 'l')}
    pico_pins(s, U, left, right, nc=('37', '34', '35'))
    pico_power(s, U, D2, 95.25, with_3v3=False)
    s.stub('RUN', U.p('30'), 'L', kind='hierarchical_label', shape='bidirectional')

    # ---- HDMI
    s.text('HDMI (HSTX, GP12–GP19): una resistencia en serie por señal', 279.4, 96.52, 1.5)
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    s.wire(R42.p('2'), hp)
    k = R42.p('1')
    s.wire(k, (k[0] - 3.81, k[1]), (k[0] - 7.62, k[1]))
    s.label('HDMI_HPD', (k[0] - 7.62, k[1]), 'L')
    R43 = s.sym('R43', 'Device:R', k[0] - 3.81, k[1] + 6.35, 0, value='100k', footprint=R0805, lcsc='C149504',
                fields={'Reference': (k[0] - 1.27, k[1] + 5.08, 'left'), 'Value': (k[0] - 1.27, k[1] + 7.62, 'left')})
    s.wire((k[0] - 3.81, k[1]), R43.p('1'))
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
    # ---- VBLANK y canal de vuelta
    s.text('Al enlace: 33 Ω junto al emisor', 279.4, 191.77, 1.5)
    resistor_row(s, 'R31', 304.8, 200.66, 'ULA_VBLANK', 'LINK_VBLANK', '33', right_kind='hierarchical_label',
                 right_shape='output', hide_value=False)
    resistor_row(s, 'R32', 304.8, 210.82, 'ULA_BACK', 'LINK_BACK', '33', right_kind='hierarchical_label',
                 right_shape='output', hide_value=False)

    # ---- Audio
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    SW2 = s.sym('SW2', 'Switch:SW_Push', 63.5, 109.22, 0, value='Modo de vídeo', footprint=PULSADOR, lcsc='C231320',
                dnp=True)
    s.wire(SW2.p('1'), (50.8, 109.22))
    s.label('MODE_BTN', (50.8, 109.22), 'L')
    p = SW2.p('2')
    s.wire(p, (p[0] + 5.08, p[1]), (p[0] + 5.08, p[1] + 2.54))
    s.pwr('GND', (p[0] + 5.08, p[1] + 2.54))
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

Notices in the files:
pcb/README.md:
8. Licencia:
La placa es hardware abierto con la licencia **CERN-OHL-W v2** (débilmente
recíproca): se puede fabricar, cambiar y vender; quien reparta el diseño
cambiado lo reparte con la misma licencia, pero lo que se le añada como pieza
aparte (un módulo, una caja, el firmware) puede llevar la suya. El texto está
en [`LICENSE`](LICENSE) y el aviso, con las excepciones, en [`NOTICE`](NOTICE):
- `tools/` es MIT ([`tools/LICENSE`](tools/LICENSE)).
- Las huellas copiadas de las bibliotecas de KiCad (el jack, el LED, la Pico 2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
